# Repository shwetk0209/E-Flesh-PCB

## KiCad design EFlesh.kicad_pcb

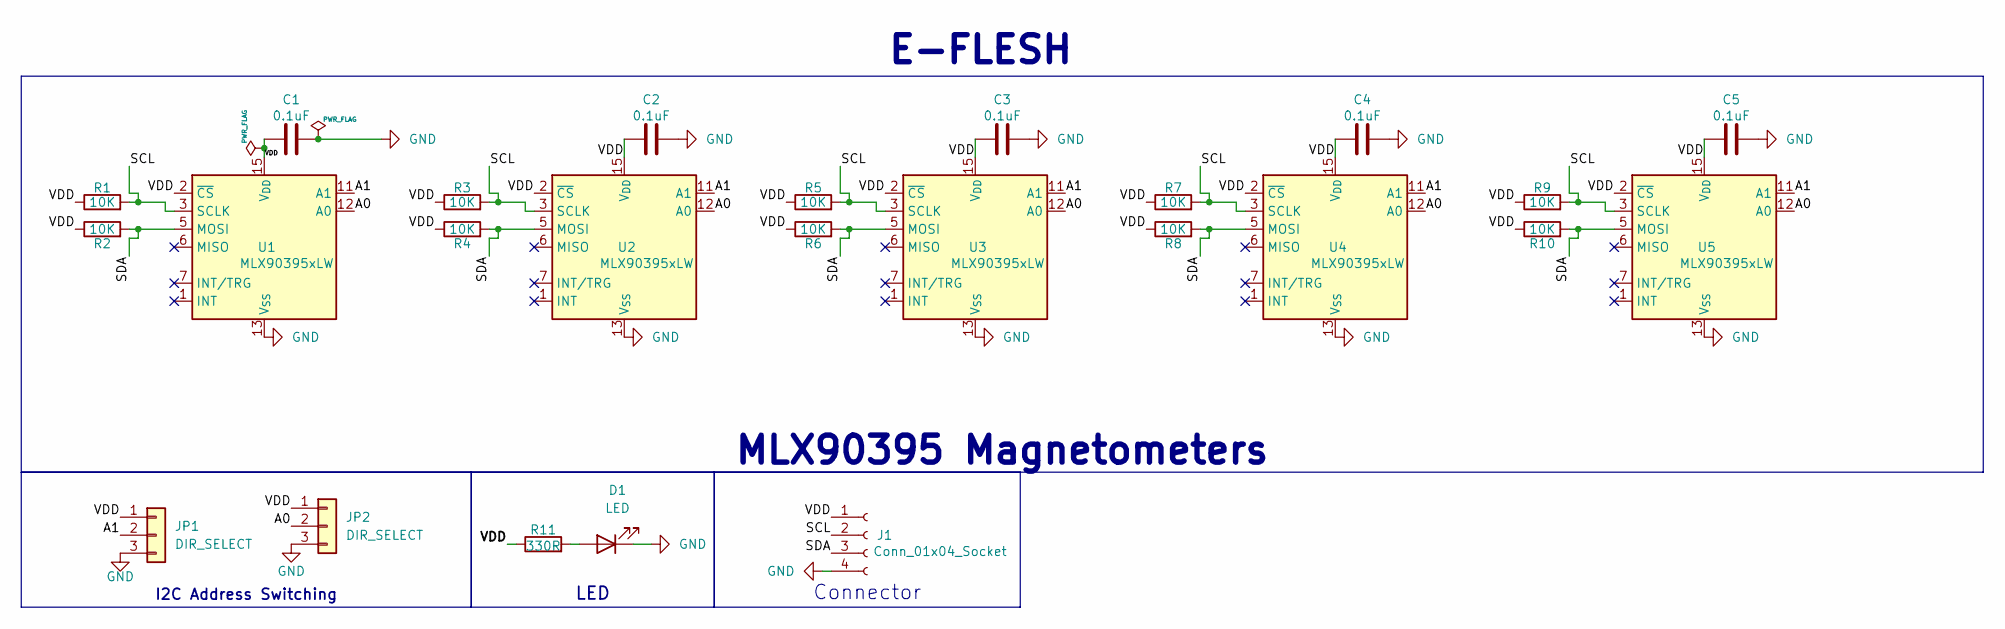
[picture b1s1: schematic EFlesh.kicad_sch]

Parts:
C1, C2, C3, C4, C5: 0.1uF; C_0805_2012Metric
D1: LED; LED_0805_2012Metric
J1: Conn_01x04_Socket; JST_EH_S4B-EH_1x04_P2.50mm_Horizontal
JP1, JP2: DIR_SELECT; SolderJumper-3_P1.3mm_Open_Pad1.0x1.5mm
R1, R2, R3, R4, R5, R6, R7, R8, R9, R10: 10K; R_0805_2012Metric
R11: 330R; R_0805_2012Metric
U1, U2, U3, U4, U5: MLX90395xLW; QFN-16-1EP_3x3mm_P0.5mm_EP1.675x1.675mm

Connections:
/A0: JP2.2, U1.12 (A0), U2.12 (A0), U3.12 (A0), U4.12 (A0), U5.12 (A0)
/A1: JP1.2, U1.11 (A1), U2.11 (A1), U3.11 (A1), U4.11 (A1), U5.11 (A1)
/SCL: J1.2, R1.2, R3.2, R5.2, R7.2, R9.2, U1.3 (SCLK), U2.3 (SCLK), U3.3 (SCLK), U4.3 (SCLK), U5.3 (SCLK)
/SDA: J1.3, R2.2, R4.2, R6.2, R8.2, R10.2, U1.5 (MOSI), U2.5 (MOSI), U3.5 (MOSI), U4.5 (MOSI), U5.5 (MOSI)
/VDD: C1.1, C2.1, C3.1, C4.1, C5.1, J1.1, JP1.1, JP2.1, R1.1, R2.1, R3.1, R4.1, R5.1, R6.1, R7.1, R8.1, R9.1, R10.1, R11.1, U1.2 (~CS), U1.15 (V_{DD}), U2.2 (~CS), U2.15 (V_{DD}), U3.2 (~CS), U3.15 (V_{DD}), U4.2 (~CS), U4.15 (V_{DD}), U5.2 (~CS), U5.15 (V_{DD})
GND: C1.2, C2.2, C3.2, C4.2, C5.2, D1.1 (K), J1.4, JP1.3, JP2.3, U1.4 (V_{SS}), U1.8 (V_{SS}), U1.9 (V_{SS}), U1.10 (V_{SS}), U1.13 (V_{SS}), U1.14 (V_{SS}), U1.16 (V_{SS}), U1.17 (V_{SS}), U2.4 (V_{SS}), U2.8 (V_{SS}), U2.9 (V_{SS}), U2.10 (V_{SS}), U2.13 (V_{SS}), U2.14 (V_{SS}), U2.16 (V_{SS}), U2.17 (V_{SS}), U3.4 (V_{SS}), U3.8 (V_{SS}), U3.9 (V_{SS}), U3.10 (V_{SS}), U3.13 (V_{SS}), U3.14 (V_{SS}), U3.16 (V_{SS}), U3.17 (V_{SS}), U4.4 (V_{SS}), U4.8 (V_{SS}), U4.9 (V_{SS}), U4.10 (V_{SS}), U4.13 (V_{SS}), U4.14 (V_{SS}), U4.16 (V_{SS}), U4.17 (V_{SS}), U5.4 (V_{SS}), U5.8 (V_{SS}), U5.9 (V_{SS}), U5.10 (V_{SS}), U5.13 (V_{SS}), U5.14 (V_{SS}), U5.16 (V_{SS}), U5.17 (V_{SS})
unnamed: D1.2 (A), R11.2

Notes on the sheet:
E-FLESH
LED
I2C Address Switching
MLX90395 Magnetometers
Connector

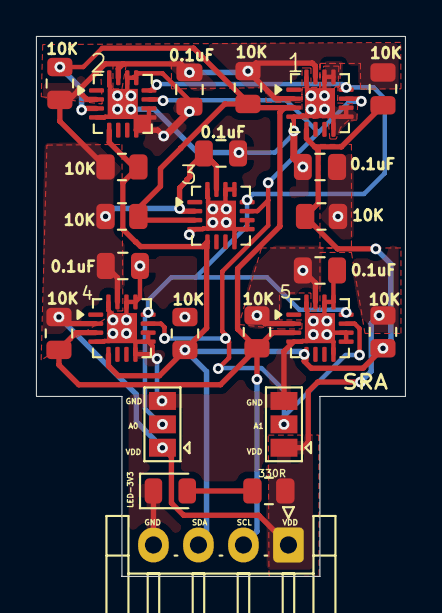
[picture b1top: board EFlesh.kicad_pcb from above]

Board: 2 copper layers, 20.5 x 30.0 mm, 25 parts (0 on the bottom side), 7 nets.
